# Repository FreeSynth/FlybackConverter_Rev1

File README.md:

# FlybackConverter_Rev1

Repository of design files for a DC-DC switchmode power supply designed for use with modular synthesiser systems.

Design by FreeSynth - Licensed under CERN-OHL-W v2

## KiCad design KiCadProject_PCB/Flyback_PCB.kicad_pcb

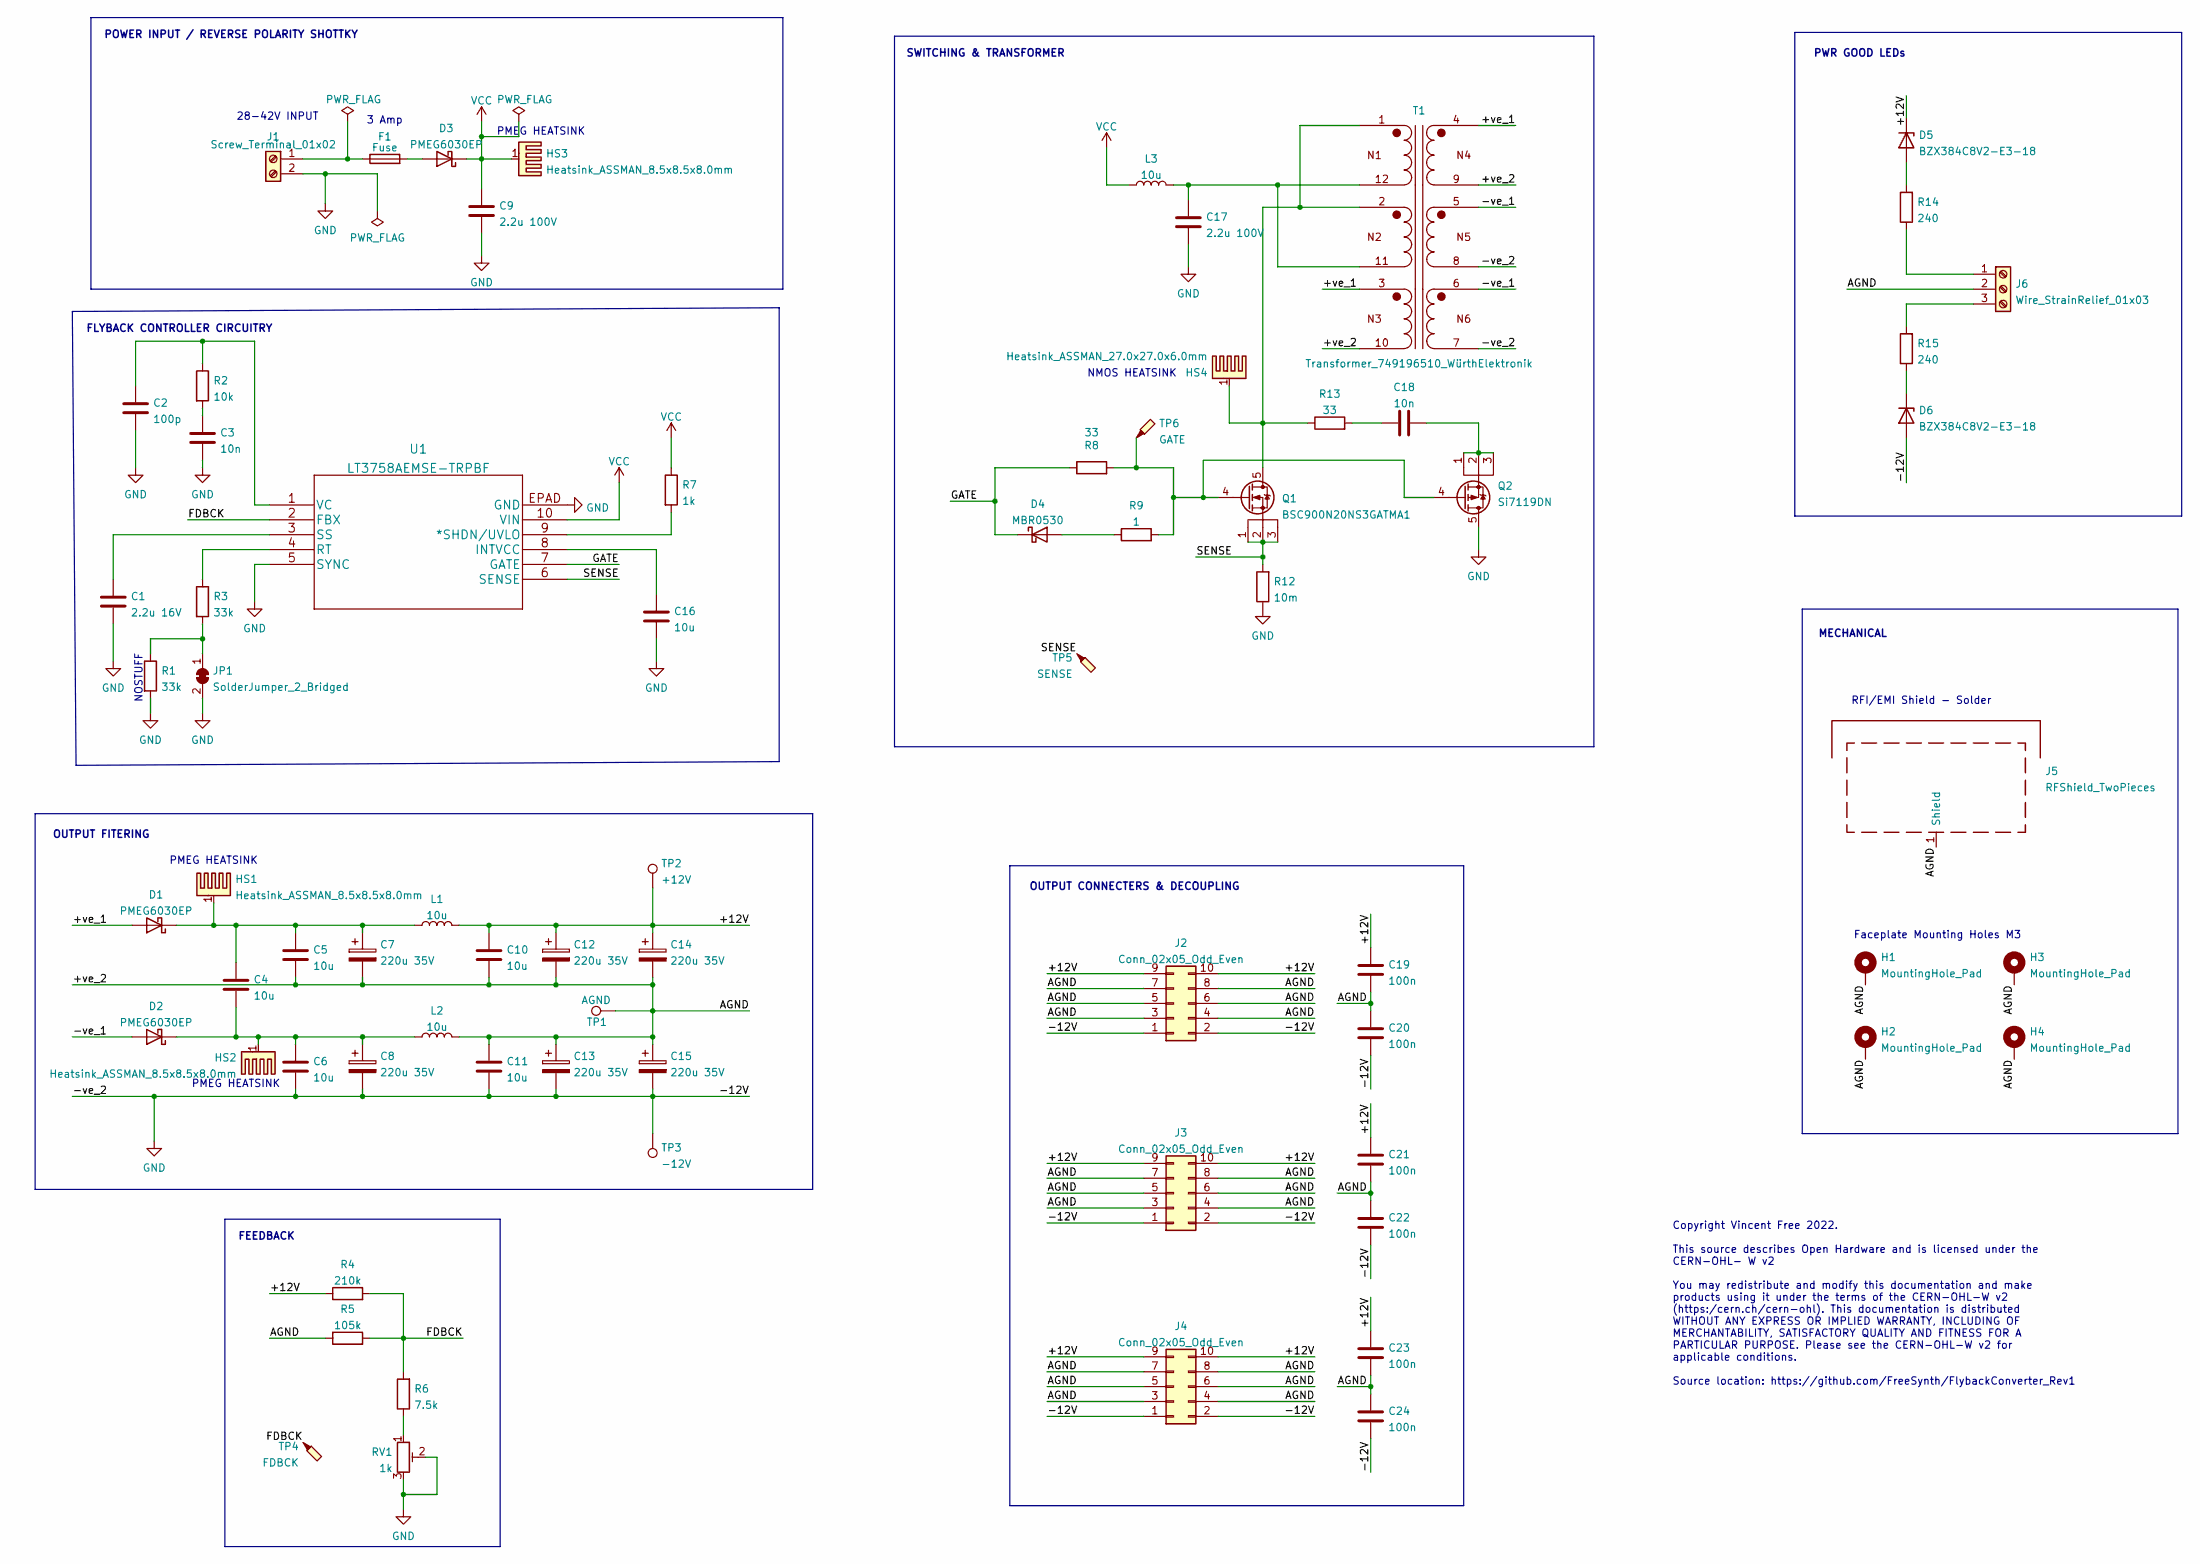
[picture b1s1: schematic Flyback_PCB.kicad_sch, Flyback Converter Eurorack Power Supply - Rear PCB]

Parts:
C1: 2.2u 16V; C_0805_2012Metric
C2: 100p; C_0805_2012Metric
C3, C18: 10n; C_0805_2012Metric
C4, C5, C6, C10, C11, C16: 10u; C_1206_3216Metric
C7, C8, C12, C13, C14, C15: 220u 35V; CP_Elec_10x10
C9, C17: 2.2u 100V; C_1206_3216Metric
C19, C20, C21, C22, C23, C24: 100n; C_0805_2012Metric
D1, D2, D3: PMEG6030EP; D_SOD-128
D4: MBR0530; D_SOD-123
D5, D6: BZX384C8V2-E3-18; D_SOD-323
F1: Fuse; 0680L-BelFuse
H1, H2, H3, H4: MountingHole_Pad; MountingHole_3.2mm_M3_DIN965_Pad
HS1, HS2, HS3: Heatsink_ASSMAN_8.5x8.5x8.0mm
HS4: Heatsink_ASSMAN_27.0x27.0x6.0mm
J1: Screw_Terminal_01x02; WürthElektronik_TermBlock_1x02_WR-TBLSeries1377_P5.00mm
J2, J3, J4: Conn_02x05_Odd_Even; IDC-Header_2x05_P2.54mm_Vertical
J5: RFShield_TwoPieces; MS638-10
J6: Wire_StrainRelief_01x03; SolderWire-0.5sqmm_1x03_P4.8mm_D0.9mm_OD2.3mm_Relief
JP1: SolderJumper_2_Bridged; SolderJumper-2_P1.3mm_Bridged_RoundedPad1.0x1.5mm
L1, L2, L3: 10u; BWVS00606045100ML1-YAGEO
Q1: BSC900N20NS3GATMA1; TDSON-8-1
Q2: Si7119DN; Vishay_PowerPAK_1212-8_Single
R1, R3: 33k; R_0805_2012Metric
R2: 10k; R_0805_2012Metric
R4: 210k; R_0805_2012Metric
R5: 105k; R_0805_2012Metric
R6: 7.5k; R_0805_2012Metric
R7: 1k; R_0805_2012Metric
R8, R13: 33; R_0805_2012Metric
R9: 1; R_0805_2012Metric
R12: 10m; R_0805_2012Metric
R14, R15: 240; R_0805_2012Metric
RV1: 1k; Potentiometer_Bourns_3296X_Horizontal
T1: Transformer_749196510_WürthElektronik
TP1: AGND; TestPoint_THTPad_D2.0mm_Drill1.0mm
TP2: +12V; TestPoint_THTPad_D2.0mm_Drill1.0mm
TP3: -12V; TestPoint_THTPad_D2.0mm_Drill1.0mm
TP4: FDBCK; TestPoint_Pad_D2.0mm
TP5: SENSE; TestPoint_Pad_D2.0mm
TP6: GATE; TestPoint_Pad_D2.0mm
U1: LT3758AEMSE-TRPBF; MSOP-10-1EP_3x3mm_P0.5mm_EP1.68x1.88mm

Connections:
/+12V: C10.2, C12.1, C14.1, C19.1, C21.1, C23.1, D5.1 (K), J2.9, J2.10, J3.9, J3.10, J4.9, J4.10, L1.2, R4.1, TP2.1
/+ve_1: D1.2 (A), T1.3, T1.4
/+ve_2: C5.1, C7.2, C10.1, C11.2, C12.2, C13.1, C14.2, C15.1, C19.2, C20.1, C21.2, C22.1, C23.2, C24.1, H1.1, H2.1, H3.1, H4.1, J2.3, J2.4, J2.5, J2.6, J2.7, J2.8, J3.3, J3.4, J3.5, J3.6, J3.7, J3.8, J4.3, J4.4, J4.5, J4.6, J4.7, J4.8, J5.1 (Shield), J6.2, L2.2, R5.1, T1.9, T1.10, TP1.1
/-ve_1: D2.2 (A), T1.5, T1.6
/FDBCK: R4.2, R5.2, R6.2, TP4.1, U1.2 (FBX)
/GATE: D4.1 (K), R8.1, U1.7 (GATE)
/SENSE: Q1.1 (S), Q1.2 (S), Q1.3 (S), R12.2, TP5.1, U1.6 (SENSE)
GND: C1.2, C2.2, C3.2, C6.1, C8.2, C9.2, C11.1, C13.2, C15.2, C16.1, C17.2, C20.2, C22.2, C24.2, D6.2 (A), J1.2, J2.1, J2.2, J3.1, J3.2, J4.1, J4.2, JP1.2 (B), Q2.5 (D), R1.2, R12.1, RV1.2, RV1.3, T1.7, T1.8, TP3.1, U1.5 (SYNC), U1.EPAD (GND)
unnamed: C1.1, U1.3 (SS)
unnamed: C2.1, R2.1, U1.1 (VC)
unnamed: C3.1, R2.2
unnamed: C4.1, C6.2, C8.1, D2.1 (K), HS2.1, L2.1
unnamed: C4.2, C5.2, C7.1, D1.1 (K), HS1.1, L1.1
unnamed: C16.2, U1.8 (INTVCC)
unnamed: C17.1, L3.2, T1.11, T1.12
unnamed: C18.1, R13.2
unnamed: C18.2, Q2.1 (S), Q2.2 (S), Q2.3 (S)
unnamed: D3.2 (A), F1.2
unnamed: D4.2 (A), R9.1
unnamed: D5.2 (A), R14.2
unnamed: D6.1 (K), R15.1
unnamed: F1.1, J1.1
unnamed: HS4.1, Q1.5 (D), R13.1, T1.1, T1.2
unnamed: J6.1, R14.1
unnamed: J6.3, R15.2
unnamed: JP1.1 (A), R1.1, R3.2
unnamed: Q1.4 (G), Q2.4 (G), R8.2, R9.2, TP6.1
unnamed: R3.1, U1.4 (RT)
unnamed: R6.1, RV1.1
unnamed: R7.2, U1.9 (*SHDN/UVLO)
VCC: C9.1, D3.1 (K), HS3.1, L3.1, R7.1, U1.10 (VIN)

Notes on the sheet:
28-42V INPUT
PWR GOOD LEDs
OUTPUT CONNECTERS & DECOUPLING
NMOS HEATSINK
MECHANICAL
SWITCHING & TRANSFORMER
PMEG HEATSINK
Faceplate Mounting Holes M3
FEEDBACK
OUTPUT FITERING
NOSTUFF
Copyright Vincent Free 2022. This source describes Open Hardware and is licensed under the CERN-OHL- W v2 You may redistribute and modify this documentation and make products using it under the terms of the CERN-OHL-W v2 (https:/cern.ch/cern-ohl). This documentation is distributed WITHOUT ANY EXPRE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
3 Amp
FLYBACK CONTROLLER CIRCUITRY
RFI/EMI Shield - Solder
POWER INPUT / REVERSE POLARITY SHOTTKY

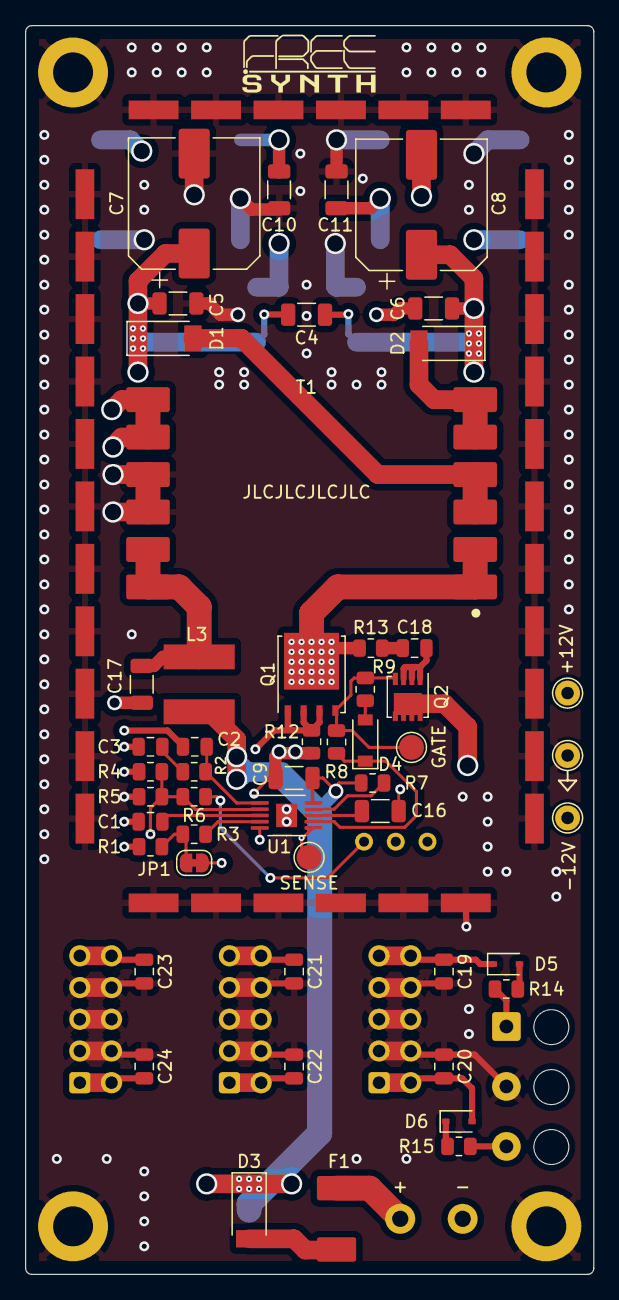
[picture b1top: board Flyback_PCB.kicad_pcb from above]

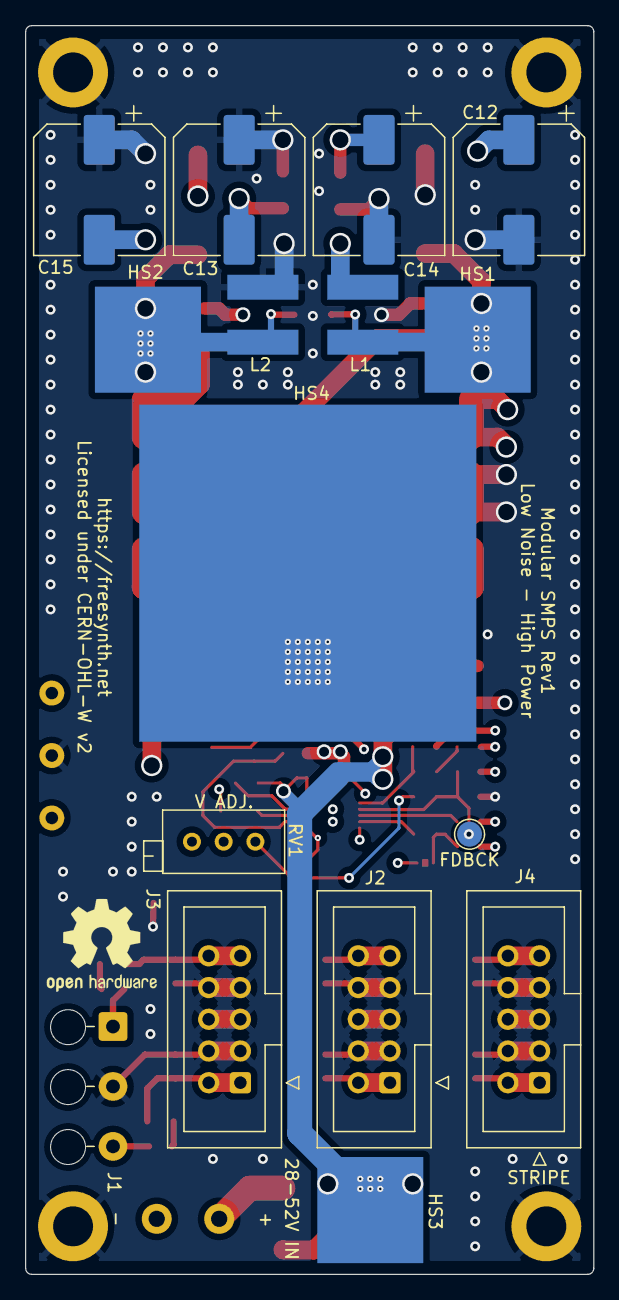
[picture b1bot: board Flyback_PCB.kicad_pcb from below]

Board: 4 copper layers, 45.5 x 100.0 mm, 73 parts (17 on the bottom side), 31 nets.

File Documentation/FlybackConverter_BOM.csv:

Faceplate / mechanical BOM,,,,,,
Item,Qty,Reference(s),Value,LibPart,Footprint,Datasheet
1,3,"ADH1, ADH2, ADH3",AdhesiveTape_8x8mm,Mechanical:AdhesiveTape,,
2,1,ADH4,AdhesiveTape_26x26mm,Mechanical:AdhesiveTape,,
3,2,"D1, D2",LED,Device:LED,SynthDIY:LED_156120VS75300_W√ºrth_ReverseMount,https://www.we-online.com/katalog/datasheet/156120VS75300.pdf
4,1,J1,Conn_01x03,Connector_Generic:Conn_01x03,SynthDIY:Kyocera_ConnectorPushInWire_009296003553906,~
5,4,"SC1, SC2, SC3, SC4",Screw_M3,Mechanical:Screw,,
6,8,"SC5, SC6, SC7, SC8, SC9, SC10, SC11, SC12",Screw_4-40,Mechanical:Screw,,
7,4,"SO1, SO2, SO3, SO4","Standoff_AluminumHex_L1/2""_1/4-40",Mechanical:Standoff,,
8,4,"WR1, WR2, WR3, WR4",Washer_M3,Mechanical:Washer,,
9,8,"WR5, WR6, WR7, WR8, WR9, WR10, WR11, WR12",Washer_4-40,Mechanical:Washer,,
,,,,,,
,,,,,,
PCB BOM,,,,,,
Item,Qty,Reference(s),Value,LibPart,Footprint,Datasheet
1,1,C1,2.2u 16V,Device:C,Capacitor_SMD:C_0805_2012Metric,~
2,1,C2,100p,Device:C,Capacitor_SMD:C_0805_2012Metric,~
3,2,"C3, C18",10n,Device:C,Capacitor_SMD:C_0805_2012Metric,~
4,6,"C4, C5, C6, C10, C11, C16",10u,Device:C,Capacitor_SMD:C_1206_3216Metric,~
5,6,"C7, C8, C12, C13, C14, C15",220u 35V,Device:C_Polarized,Capacitor_SMD:CP_Elec_10x10,~
6,2,"C9, C17",2.2u 100V,Device:C,Capacitor_SMD:C_1206_3216Metric,~
7,6,"C19, C20, C21, C22, C23, C24",100n,Device:C,Capacitor_SMD:C_0805_2012Metric,~
8,3,"D1, D2, D3",PMEG6030EP,Diode:PMEG6030EP,Diode_SMD:D_SOD-128,https://assets.nexperia.com/documents/data-sheet/PMEG6030EP.pdf
9,1,D4,MBR0530,Diode:MBR0530,Diode_SMD:D_SOD-123,http://www.mccsemi.com/up_pdf/MBR0520~MBR0580(SOD123).pdf
10,2,"D5, D6",BZX384C8V2-E3-18,Diode:BZX384-xxx,Diode_SMD:D_SOD-323,https://www.vishay.com/docs/85764/bzx384.pdf
11,1,F1,Fuse,Device:Fuse,Fuse:0680L-BelFuse,~
12,3,"HS1, HS2, HS3",Heatsink_ASSMAN_8.5x8.5x8.0mm,Mechanical:Heatsink_Pad,Heatsink:Heatsink_ASSMAN_8.5x8.5x8.0mm,~
13,1,HS4,Heatsink_ASSMAN_27.0x27.0x6.0mm,Mechanical:Heatsink_Pad,Heatsink:Heatsink_ASSMAN_27.0x27.0x6.0mm,~
14,1,J1,Screw_Terminal_01x02,Connector:Screw_Terminal_01x02,TerminalBlock_Wuerth:W√ºrthElektronik_TermBlock_1x02_WR-TBLSeries1377_P5.00mm,~
15,3,"J2, J3, J4",Conn_02x05_Odd_Even,Connector_Generic:Conn_02x05_Odd_Even,Connector_IDC:IDC-Header_2x05_P2.54mm_Vertical,~
16,1,J5,RFShield_TwoPieces,Device:RFShield_TwoPieces,RF_Shielding:MS638-10,~
17,1,JP1,SolderJumper_2_Bridged,Jumper:SolderJumper_2_Bridged,Jumper:SolderJumper-2_P1.3mm_Bridged_RoundedPad1.0x1.5mm,~
18,3,"L1, L2, L3",10u,Device:L,Inductor_SMD:BWVS00606045100ML1-YAGEO,~
19,1,Q1,BSC900N20NS3GATMA1,Device:BSC900N20NS3GATMA1,Package_TO_SOT_SMD:TDSON-8-1,https://www.infineon.com/dgdl/BSC900N20NS3+Rev2.1.pdf?folder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
20,1,Q2,Si7119DN,Device:Si7119DN,Package_SO:Vishay_PowerPAK_1212-8_Single,https://www.vishay.com/docs/74251/si7119dn.pdf
21,2,"R1, R3",33k,Device:R,Resistor_SMD:R_0805_2012Metric,~
22,1,R2,10k,Device:R,Resistor_SMD:R_0805_2012Metric,~
23,1,R4,210k,Device:R,Resistor_SMD:R_0805_2012Metric,~
24,1,R5,105k,Device:R,Resistor_SMD:R_0805_2012Metric,~
25,1,R6,7.5k,Device:R,Resistor_SMD:R_0805_2012Metric,~
26,1,R7,1k,Device:R,Resistor_SMD:R_0805_2012Metric,~
27,2,"R8, R13",33,Device:R,Resistor_SMD:R_0805_2012Metric,~
28,1,R9,1,Device:R,Resistor_SMD:R_0805_2012Metric,~
29,1,R12,10m,Device:R,Resistor_SMD:R_0805_2012Metric,~
30,2,"R14, R15",240,Device:R,Resistor_SMD:R_0805_2012Metric,~
31,1,RV1,1k,Device:R_Potentiometer_Trim,Potentiometer_THT:Potentiometer_Bourns_3296X_Horizontal,~
32,1,T1,Transformer_749196510_W√ºrthElektronik,Device:Transformer_749196510_W√ºrthElektronik,Transformer_SMD:Transformer_749196510_W√ºrthElektronik,https://www.we-online.com/katalog/datasheet/749196510.pdf
33,1,U1,LT3758AEMSE-TRPBF,LT3758:LT3758AEMSE-TRPBF,Package_SO:MSOP-10-1EP_3x3mm_P0.5mm_EP1.68x1.88mm,https://www.analog.com/media/en/technical-documentation/data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

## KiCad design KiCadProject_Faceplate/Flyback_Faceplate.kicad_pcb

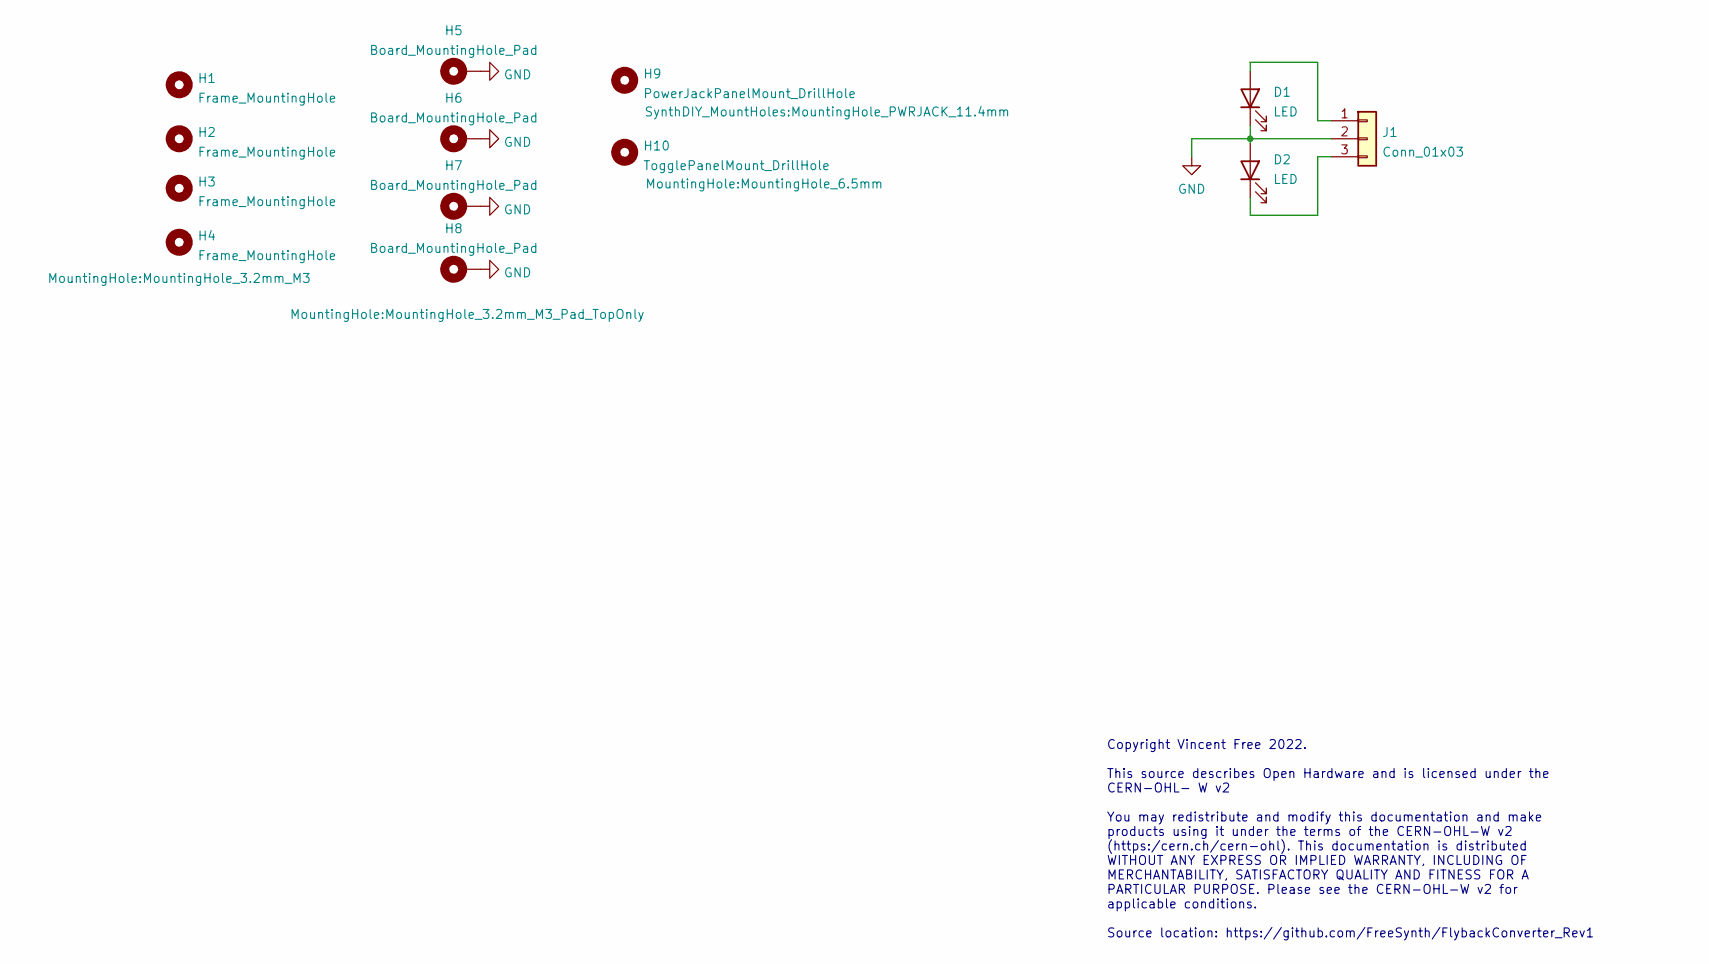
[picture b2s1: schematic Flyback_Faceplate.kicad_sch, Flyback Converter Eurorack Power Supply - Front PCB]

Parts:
D1, D2: LED; LED_156120VS75300_Würth_ReverseMount
H1, H2, H3, H4: Frame_MountingHole; MountingHole_3.2mm_M3
H5, H6, H7, H8: Board_MountingHole_Pad; MountingHole_3.2mm_M3_Pad_TopOnly
H9: PowerJackPanelMount_DrillHole; MountingHole_PWRJACK_11.4mm
H10: TogglePanelMount_DrillHole; MountingHole_6.5mm
J1: Conn_01x03; Kyocera_3pos_WireToBoard

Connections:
GND: D1.1 (K), D2.2 (A), H5.1, H6.1, H7.1, H8.1, J1.2
unnamed: D1.2 (A), J1.1
unnamed: D2.1 (K), J1.3

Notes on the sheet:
Copyright Vincent Free 2022. This source describes Open Hardware and is licensed under the CERN-OHL- W v2 You may redistribute and modify this documentation and make products using it under the terms of the CERN-OHL-W v2 (https:/cern.ch/cern-ohl). This documentation is distributed WITHOUT ANY EXPRE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

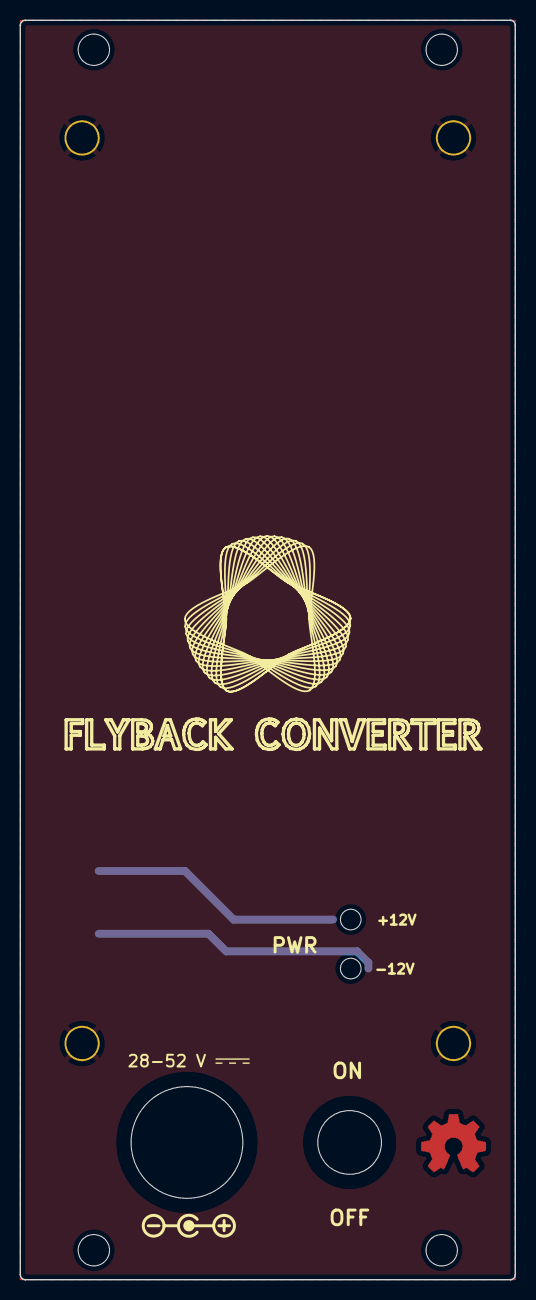
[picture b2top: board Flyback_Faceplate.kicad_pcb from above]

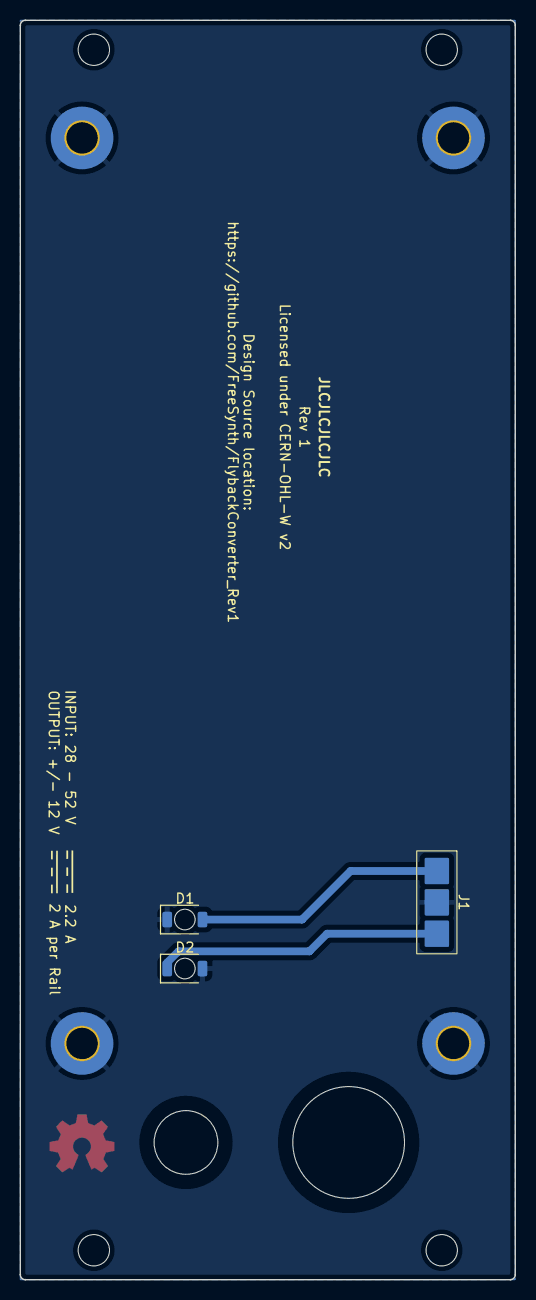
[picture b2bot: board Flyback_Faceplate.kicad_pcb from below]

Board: 2 copper layers, 50.5 x 128.5 mm, 13 parts (7 on the bottom side), 3 nets.
